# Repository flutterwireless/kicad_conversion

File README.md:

Flutter Basic KiCAD Version
==

I am working on converting Flutter (and myself) over to KiCAD.

This version is not yet ready to fab, but the copper is close and I am confident that moving to KiCAD will work.

Taylor

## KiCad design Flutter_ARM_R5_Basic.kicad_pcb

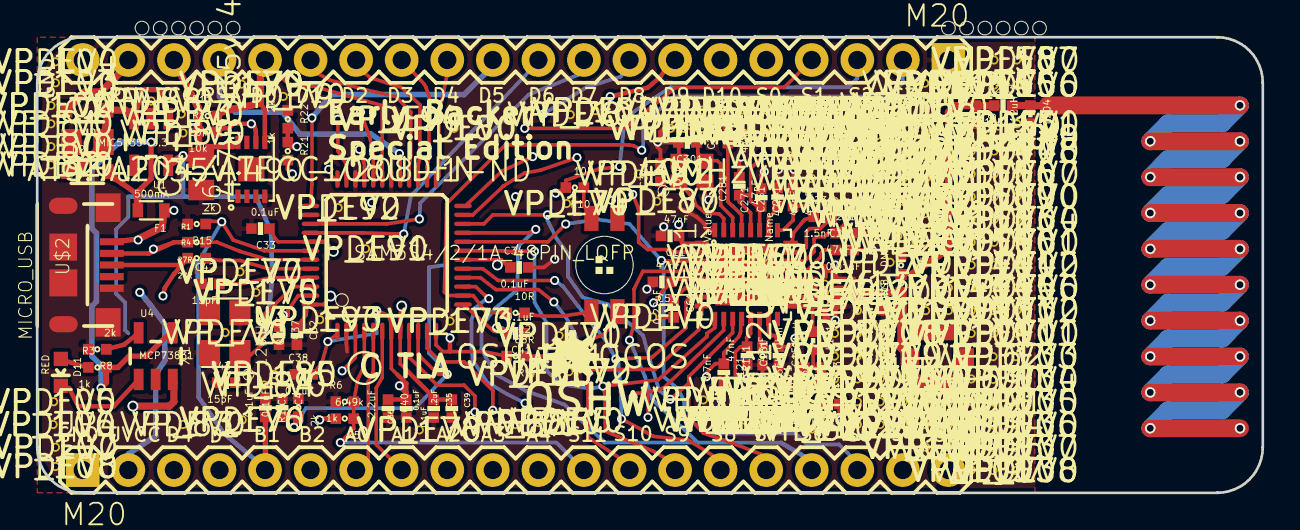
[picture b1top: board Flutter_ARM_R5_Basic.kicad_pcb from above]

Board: 4 copper layers, 68.3 x 25.4 mm, 287 parts (0 on the bottom side), 68 nets.

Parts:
@HOLE0, @HOLE1, @HOLE2, @HOLE3, @HOLE4, @HOLE5, @HOLE6, @HOLE7, @HOLE8, @HOLE9, @HOLE10, @HOLE11: (no value)
C2, C3: 4.7uF 35v 490-7208-1-ND; 0808-CAP
C4, C5, C32, C33, C34, C35, C36, C37, C38, C41: 0.1uF; 0402-CAP
C11, C51, C121, C131, C151, C221, C251, C261, C271, C281, C291: 47nF; 0402-CAP
C39, C40: 2.2uF; 0402-CAP
C42, C43, C301, C311: 15pF; 0402-CAP
C61: 0.22uF; 0402-CAP
C171, C211: 0.01uF; 0402-CAP
C172: 100pF; 0402-CAP
C173: 33pF; 0402-CAP
C203: 1pF; 0402-CAP
C231: 1.5nF; 0402-CAP
D1, D2: SOD-323
D11: RED; LED-0603
F1: 500mA; 0603-PTC
JP2, JP4: M20; 1X20
L171: 0.01uH; 0402-IND
L204: 0.012uH; 0402-IND
LED1: P-LCC-4-3
R1, R4: 27R; 0402-RES
R2, R10, R171: 10R; 0402-RES
R3, R6, R21: 1k; 0402-RES
R5: 6.49k; 0402-RES
R7, R17, R20: DNS; 0402-RES
R8, R14, R15, R22: 2k; 0402-RES
R9: 68R; 0402-RES
R11, R13: 10k; 0402-RES
R18, R19: 0R; 0402-RES
R141: 56K Ohm; 0402-RES
U1: MIC5235-3.3; SOT23-5
U2: CC1200; QFN-32
U3: SAM3S4/2/1A_48PIN_LQFP; LQFP48
U4: MCP73831; SOT23-5
U5: BALUN_CC1200; IPC_BALUN_CC1200
U6: ATSHA204/ATECC108UDFN; UDFN_8_ATSHA204
U7: U.FL
U$1: OSHW-LOGOS; OSHW-LOGO-S
U$2: MICRO_USB; MICRO-USB-SLOT-2
U$11, U$12: SNAP_DOME; 12MM_SNAP_DOME_SMALLER
VP_0, VP_1, VP_2, VP_3, VP_4, VP_5, VP_6, VP_7, VP_8, VP_9, VP_10, VP_11, VP_12, VP_13, VP_14, VP_15, VP_16, VP_17, VP_18, VP_19, VP_20, VP_21, VP_22, VP_23, VP_24, VP_25, VP_26, VP_27, VP_28, VP_29, VP_30, VP_31, VP_32, VP_33, VP_34, VP_35, VP_36, VP_37, VP_38, VP_39, VP_40, VP_41, VP_42, VP_43, VP_44, VP_45, VP_46, VP_47, VP_48, VP_49, VP_50, VP_51, VP_52, VP_53, VP_54, VP_55, VP_56, VP_57, VP_58, VP_59, VP_60, VP_61, VP_62, VP_63, VP_64, VP_65, VP_66, VP_67, VP_68, VP_69, VP_70, VP_71, VP_72, VP_73, VP_74, VP_78, VP_79, VP_80, VP_81, VP_82, VP_83, VP_84, VP_85, VP_86, VP_87, VP_88, VP_89, VP_90, VP_91, VP_92, VP_93, VP_94, VP_95, VP_96, VP_97, VP_98, VP_99, VP_100, VP_101, VP_102, VP_103, VP_104, VP_105, VP_106, VP_107, VP_108, VP_109, VP_110, VP_111, VP_112, VP_113, VP_114, VP_115, VP_116, VP_117, VP_118, VP_119, VP_120, VP_121, VP_122, VP_123, VP_124, VP_125, VP_126, VP_127, VP_128, VP_129, VP_130, VP_131, VP_132, VP_133, VP_134, VP_135, VP_136, VP_137, VP_138, VP_139, VP_140, VP_141, VP_142, VP_143, VP_144, VP_145, VP_146, VP_147, VP_148, VP_149, VP_150, VP_151, VP_152, VP_153, VP_154, VP_155, VP_156, VP_157, VP_158, VP_159, VP_160, VP_161, VP_162, VP_163, VP_164, VP_165, VP_166, VP_167, VP_168, VP_169, VP_170, VP_171, VP_172, VP_173, VP_174, VP_175, VP_176, VP_177, VP_178, VP_179, VP_180, VP_181, VP_182, VP_183, VP_184, VP_185, VP_186, VP_187, VP_188, VP_189, VP_190, VP_191, VP_192, VP_193, VP_194: VPDEV0; VPAC0
VP_75, VP_76, VP_77: VPDEV1; VPAC1
X1: 12MHz; XTAL_ABRACON_ABM8G_3.2MMX2.5MM
X2: 40MHz; XTAL_EPSON_FA_128_2MMX1.6MM

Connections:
3.3V: C3.2, C11.1, C36.2, C37.1, C38.2, C40.1, C41.2, C51.1, C121.1, C131.1, C151.1, C171.1, C172.1, C173.2, C221.1, C251.1, C271.1, C281.1, JP2.18, LED1.2, R11.1, R13.1, R171.1, U1.5, U2.1, U2.5, U2.12, U2.13, U2.15, U2.22, U2.25, U2.27, U2.28, U3.1, U3.7, U3.13, U3.33, U3.47, U6.8, U$11.P$1, U$11.P$2, U$11.P$3, U$11.P$4, U$12.P$1, U$12.P$2, U$12.P$3, U$12.P$4, VP_0.VP
+1.8V: C32.1, C33.1, C34.1, C35.1, C39.1, U3.8, U3.18, U3.41, U3.48
A0/URXD1: JP4.7, U3.5
A1/UTXD1: JP4.8, U3.6
A2: JP4.9, U3.9
A3: JP4.10, U3.11
A4: JP4.11, U3.3
ANT: C203.2, L204.1
B1/ERASE: C5.2, JP4.5, R15.1, U3.42
B2: C4.2, JP4.6, R14.1, U3.10
D0/TWD0: JP2.16, R11.2, U3.31, U6.5
D1/TWCK0: JP2.15, R13.2, U3.28, U6.6
D2/RX0: JP2.14, U3.27
D3/TX0: JP2.13, U3.26
D4/TDI: JP2.12, U3.25
D5/TDO: JP2.11, U3.37
D6/TCK: JP2.10, U3.40
D7/TMS: JP2.9, U3.39
D8: JP2.8, U3.35
D9: JP2.7, U3.32
D10: JP2.6, U3.24
GND: C2.1, C3.1, C4.1, C5.1, C11.2, C32.2, C33.2, C34.2, C35.2, C36.1, C37.2, C38.1, C39.2, C40.2, C41.1, C42.1, C43.1, C51.2, C61.2, C121.2, C131.2, C151.2, C171.2, C172.2, C211.2, C221.2, C251.2, C261.2, C271.2, C281.2, C291.2, C301.2, C311.2, JP2.1, JP2.20, JP4.1, JP4.20, L204.2, R6.1, R7.1, R8.2, R14.2, R15.2, R19.1, R20.1, R22.1, R141.1, U1.2, U2.32, U2.EP, U3.2, U3.30, U3.34, U3.38, U4.2, U5.5, U5.6, U5.8, U5.9, U5.10, U6.4, U7.P$1, U7.P$2, U$2.GND, U$2.PAD1, U$2.PAD2, U$2.PAD3, U$2.PAD4, U$2.PAD5, U$2.PAD6, U$2.PAD7, U$2.PAD8, VP_1.VP, VP_2.VP, VP_3.VP, VP_4.VP, VP_5.VP, VP_6.VP, VP_7.VP, VP_8.VP, VP_9.VP, VP_10.VP, VP_11.VP, VP_12.VP, VP_13.VP, VP_14.VP, VP_15.VP, VP_16.VP, VP_17.VP, VP_18.VP, VP_19.VP, VP_20.VP, VP_21.VP, VP_22.VP, VP_23.VP, VP_24.VP, VP_25.VP, VP_26.VP, VP_27.VP, VP_28.VP, VP_29.VP, VP_30.VP, VP_31.VP, VP_32.VP, VP_33.VP, VP_34.VP, VP_35.VP, VP_36.VP, VP_37.VP, VP_38.VP, VP_39.VP, VP_40.VP, VP_41.VP, VP_42.VP, VP_43.VP, VP_44.VP, VP_45.VP, VP_46.VP, VP_47.VP, VP_48.VP, VP_49.VP, VP_50.VP, VP_51.VP, VP_52.VP, VP_53.VP, VP_54.VP, VP_55.VP, VP_56.VP, VP_57.VP, VP_58.VP, VP_59.VP, VP_60.VP, VP_61.VP, VP_62.VP, VP_63.VP, VP_64.VP, VP_65.VP, VP_66.VP, VP_67.VP, VP_68.VP, VP_69.VP, VP_70.VP, VP_71.VP, VP_72.VP, VP_73.VP, VP_74.VP, VP_75.VP, VP_76.VP, VP_77.VP, VP_78.VP, VP_79.VP, VP_80.VP, VP_81.VP, VP_82.VP, VP_83.VP, VP_84.VP, VP_85.VP, VP_86.VP, VP_87.VP, VP_88.VP, VP_89.VP, VP_90.VP, VP_91.VP, VP_92.VP, VP_93.VP, VP_94.VP, VP_95.VP, VP_96.VP, VP_97.VP, VP_98.VP, VP_99.VP, VP_100.VP, VP_101.VP, VP_102.VP, VP_103.VP, VP_104.VP, VP_105.VP, VP_106.VP, VP_107.VP, VP_108.VP, VP_109.VP, VP_110.VP, VP_111.VP, VP_112.VP, VP_113.VP, VP_114.VP, VP_115.VP, VP_116.VP, VP_117.VP, VP_118.VP, VP_119.VP, VP_120.VP, VP_121.VP, VP_122.VP, VP_123.VP, VP_124.VP, VP_125.VP, VP_126.VP, VP_127.VP, VP_128.VP, VP_129.VP, VP_130.VP, VP_131.VP, VP_132.VP, VP_133.VP, VP_134.VP, VP_135.VP, VP_136.VP, VP_137.VP, VP_138.VP, VP_139.VP, VP_140.VP, VP_141.VP, VP_142.VP, VP_143.VP, VP_144.VP, VP_145.VP, VP_146.VP, VP_147.VP, VP_148.VP, VP_149.VP, VP_150.VP, VP_151.VP, VP_152.VP, VP_153.VP, VP_154.VP, VP_155.VP, VP_156.VP, VP_157.VP, VP_158.VP, VP_159.VP, VP_160.VP, VP_161.VP, VP_162.VP, VP_163.VP, VP_164.VP, VP_165.VP, VP_166.VP, VP_167.VP, VP_168.VP, VP_169.VP, VP_170.VP, VP_171.VP, VP_172.VP, VP_173.VP, VP_174.VP, VP_175.VP, VP_176.VP, VP_177.VP, VP_178.VP, VP_179.VP, VP_180.VP, VP_181.VP, VP_182.VP, VP_183.VP, VP_184.VP, VP_185.VP, VP_186.VP, VP_187.VP, VP_188.VP, VP_189.VP, VP_190.VP, VP_191.VP, VP_192.VP, VP_193.VP, VP_194.VP, X1.P$2, X1.P$4, X2.2, X2.4
LNA_N: U2.20, U5.1
LNA_P: U2.19, U5.2
unnamed: C61.1, U2.6
unnamed: R141.2, U2.14
unnamed: C231.1, U2.24
unnamed: C231.2, U2.23
unnamed: C211.1, U2.21
unnamed: D11.A, R3.1
unnamed: C173.1, L171.2, R171.2
unnamed: C203.1, R7.2, R18.2, R20.2
unnamed: R17.1, R18.1, U5.7
unnamed: R17.2, R19.2, U7.P$3
unnamed: C311.1, U2.31, X2.1
unnamed: C261.1, U2.26
unnamed: C301.1, U2.30, X2.3
unnamed: C291.1, U2.29
unnamed: LED1.1, R9.1
unnamed: LED1.4, R2.1
unnamed: C42.2, U3.45, X1.P$3
unnamed: C43.2, U3.46, X1.P$1
PA: L171.1, U2.17, U5.4
PROG: R8.1, U4.5
RAW: D1.2, JP2.19, R5.2, U4.3
RAW_REG: C2.2, D1.1, D2.1, U1.1, U1.3
RST: JP2.17, U2.2, U3.29
S0/UVCCDIV: JP2.5, R21.1, R22.2, U3.23
S1/R: JP2.4, R9.2, U3.12
S2/B: JP2.3, R10.2, U3.36
S3/G: JP2.2, R2.2, U3.14
S4/IO0: JP4.19, U2.10, U3.15
S5/IO3: JP4.18, U2.3, U3.20
S6/IO2: JP4.17, U2.4, U3.21
S7/CS: JP4.16, U2.11, U3.22
S8/SI: JP4.15, U2.7, U3.17
S9/SO: JP4.14, U2.9, U3.19
S10/CK: JP4.13, U2.8, U3.16
S11/A5: JP4.12, R5.1, R6.2, U3.4
STAT: D11.C, U4.1
TRX_SW: U2.18, U5.3
U7: LED1.3, R10.1
UDDC_+: R4.2, U3.44
UDDC_-: R1.2, U3.43
UDDM: JP4.4, R1.1, U$2.D-
UDDP: JP4.3, R4.1, U$2.D+
UVCC: F1.1, JP4.2, R21.2, U$2.VBUS
UVCC_FUSED: D2.2, F1.2, R3.2, U4.4

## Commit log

2018-01-29 Initial Commit. Converting Flutter Basic to KiCAD.
2018-01-29 Add Readme

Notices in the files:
Flutter_ARM_R5_Basic.kicad_pcb:
Released under the Creative Commons Attribution Share-Alike 4.0 License
http://creativecommons.org/licenses/by-sa/4.0
